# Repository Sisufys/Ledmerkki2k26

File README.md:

The quest for the coolest led overall patch continues....

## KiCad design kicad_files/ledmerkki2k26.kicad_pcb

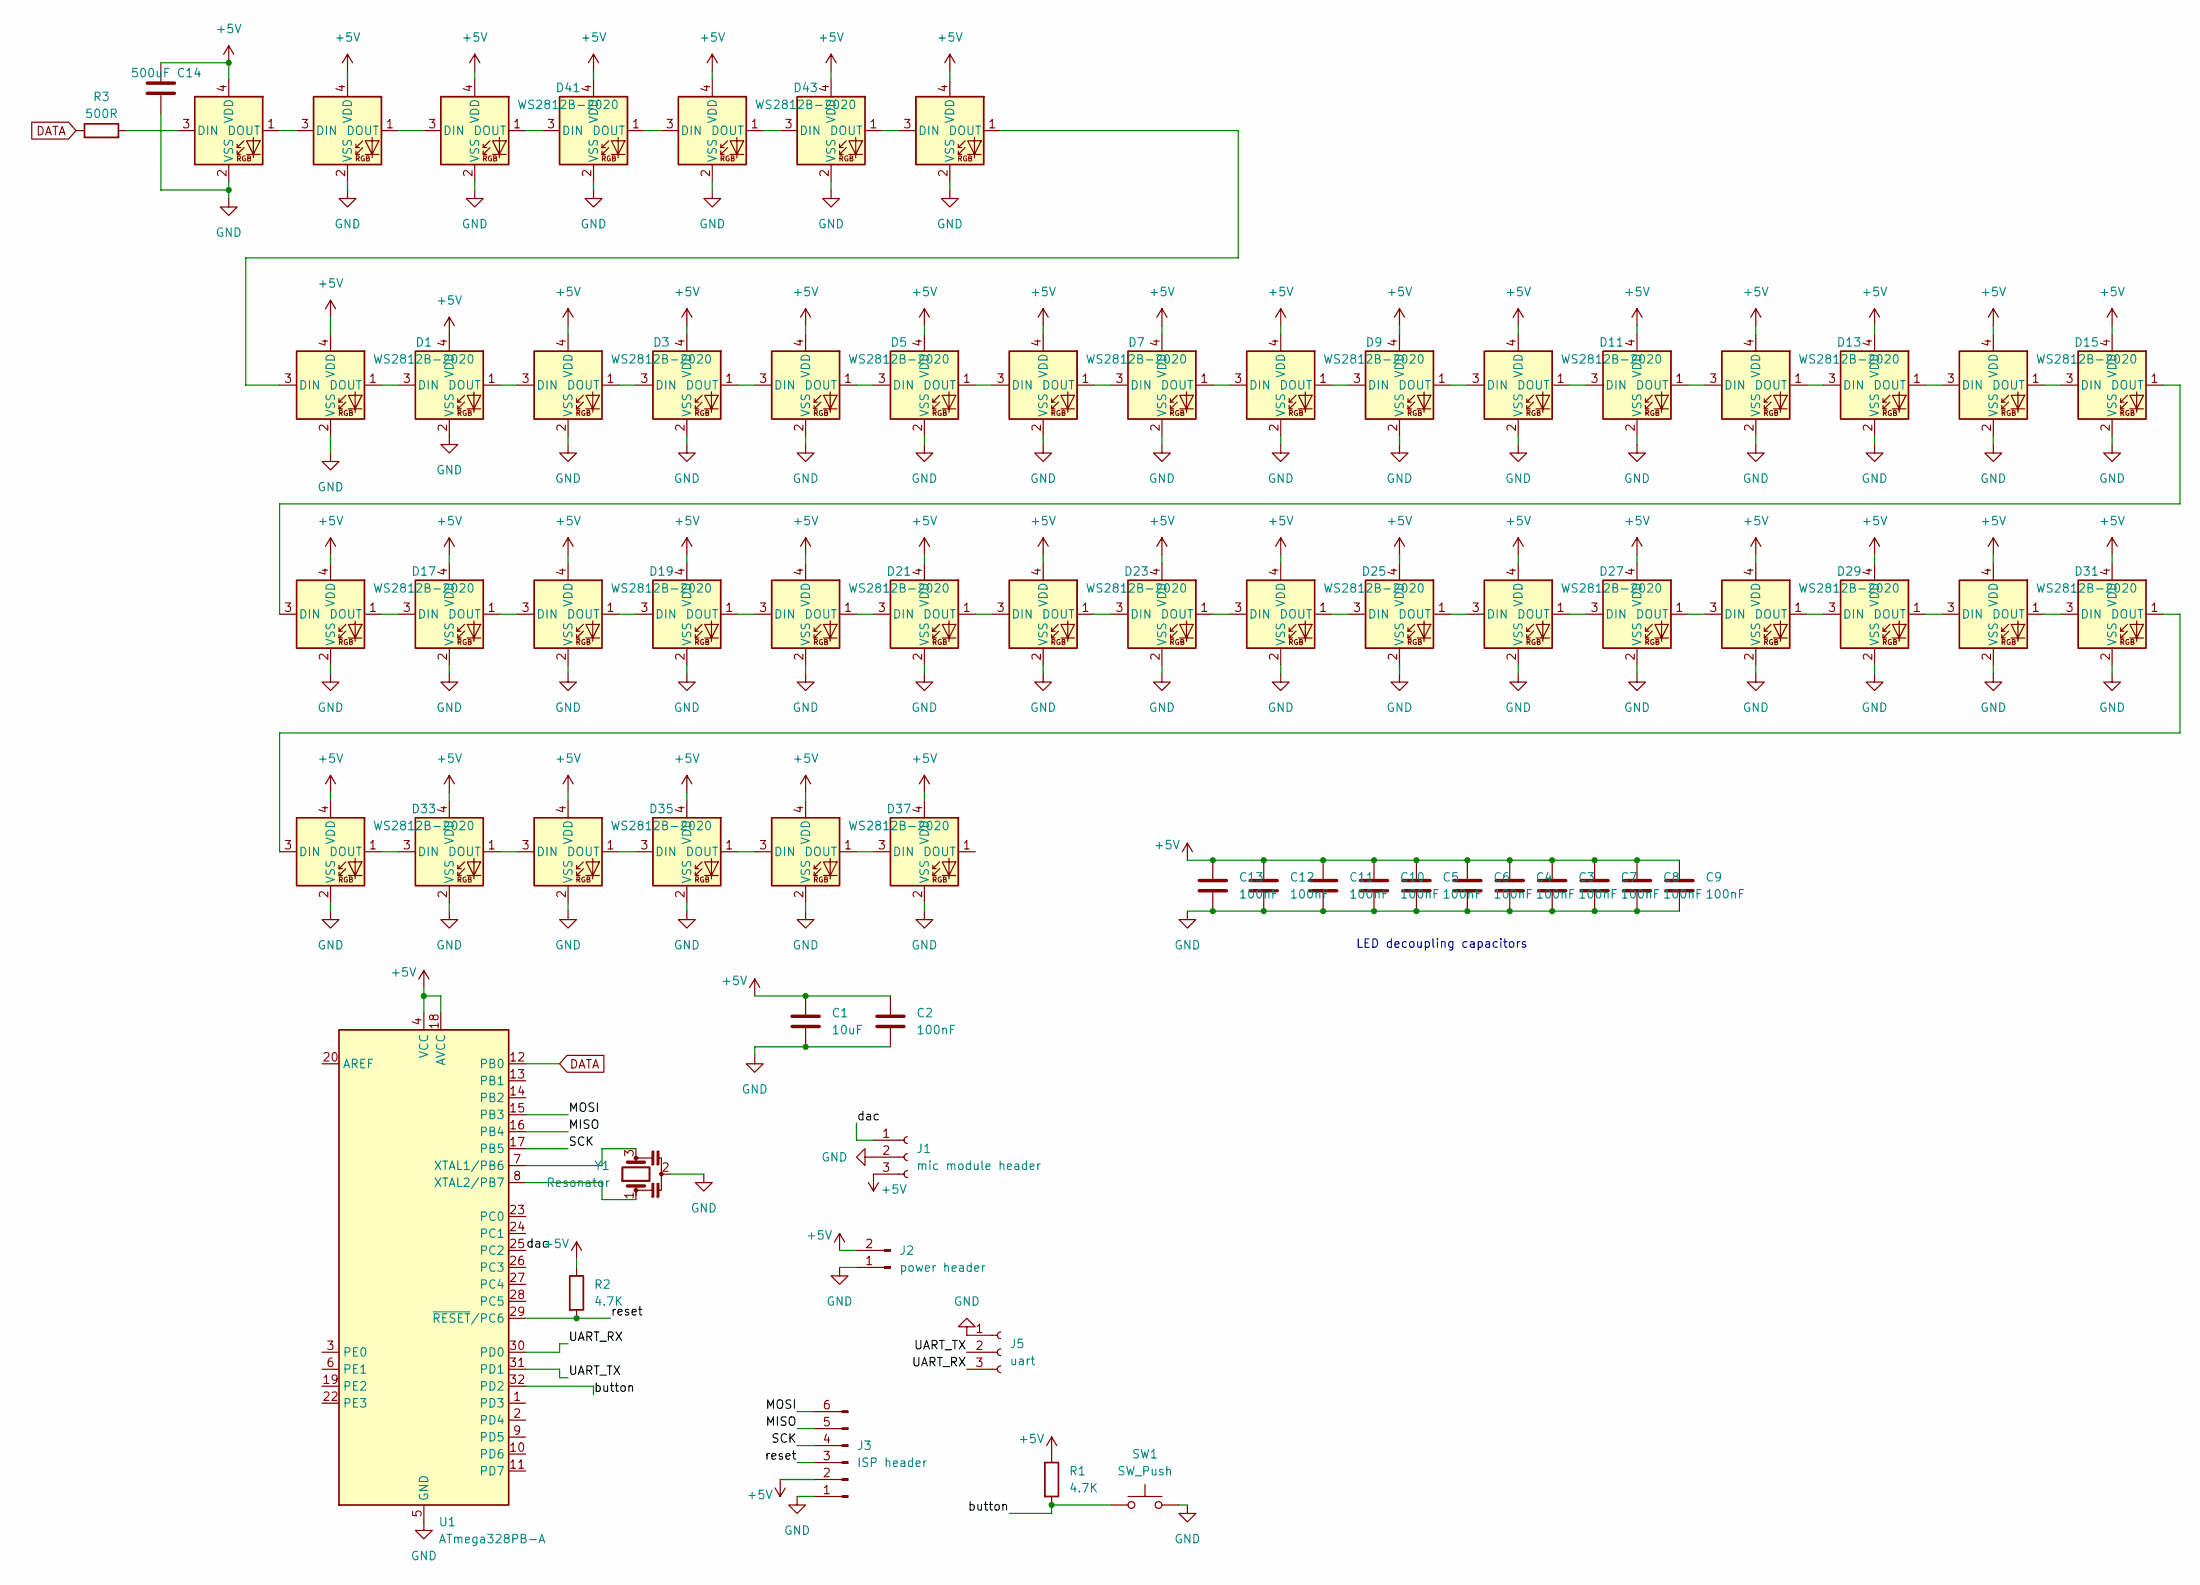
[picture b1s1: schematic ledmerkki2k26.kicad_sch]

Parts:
C1: 10uF; C_1206_3216Metric_Pad1.33x1.80mm_HandSolder
C2, C3, C4, C5, C6, C7, C8, C9, C10, C11, C12, C13: 100nF; C_1206_3216Metric_Pad1.33x1.80mm_HandSolder
C14: 500uF; CP_EIA-7343-15_Kemet-W_HandSolder
D1, D2, D3, D4, D5, D6, D7, D8, D9, D10, D11, D12, D13, D14, D15, D16, D17, D18, D19, D20, D21, D22, D23, D24, D25, D26, D27, D28, D29, D30, D31, D32, D33, D34, D35, D36, D37, D38, D39, D40, D41, D42, D43, D44, D45: WS2812B-2020; LED_WS2812B-2020_PLCC4_2.0x2.0mm
J1: mic module header; PinSocket_1x03_P2.54mm_Vertical
J2: power header; PinHeader_1x02_P2.54mm_Vertical
J3: ISP header; PinHeader_1x06_P2.54mm_Horizontal
J5: uart; PinSocket_1x03_P2.54mm_Vertical
R1, R2: 4.7K; R_0805_2012Metric_Pad1.20x1.40mm_HandSolder
R3: 500R; LED_0805_2012Metric_Pad1.15x1.40mm_HandSolder
SW1: SW_Push; SW_PUSH_6mm
U1: ATmega328PB-A; TQFP-32_7x7mm_P0.8mm
Y1: Resonator; Resonator_SMD_Murata_CSTxExxV-3Pin_3.0x1.1mm_HandSoldering

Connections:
+5V: C1.1, C2.1, C3.1, C4.1, C5.1, C6.1, C7.1, C8.1, C9.1, C10.1, C11.1, C12.1, C13.1, C14.1, D1.4 (VDD), D2.4 (VDD), D3.4 (VDD), D4.4 (VDD), D5.4 (VDD), D6.4 (VDD), D7.4 (VDD), D8.4 (VDD), D9.4 (VDD), D10.4 (VDD), D11.4 (VDD), D12.4 (VDD), D13.4 (VDD), D14.4 (VDD), D15.4 (VDD), D16.4 (VDD), D17.4 (VDD), D18.4 (VDD), D19.4 (VDD), D20.4 (VDD), D21.4 (VDD), D22.4 (VDD), D23.4 (VDD), D24.4 (VDD), D25.4 (VDD), D26.4 (VDD), D27.4 (VDD), D28.4 (VDD), D29.4 (VDD), D30.4 (VDD), D31.4 (VDD), D32.4 (VDD), D33.4 (VDD), D34.4 (VDD), D35.4 (VDD), D36.4 (VDD), D37.4 (VDD), D38.4 (VDD), D39.4 (VDD), D40.4 (VDD), D41.4 (VDD), D42.4 (VDD), D43.4 (VDD), D44.4 (VDD), D45.4 (VDD), J1.3, J2.2, J3.2, R1.1, R2.1, U1.4 (VCC), U1.18 (AVCC); also elsewhere on the board
/MISO: J3.5, U1.16 (PB4)
/MOSI: J3.6, U1.15 (PB3)
/SCK: J3.4, U1.17 (PB5)
/UART_RX: J5.3, U1.30 (PD0)
/UART_TX: J5.2, U1.31 (PD1)
/button: R1.2, SW1.1, U1.32 (PD2)
/dac: J1.1, U1.25 (PC2)
/reset: J3.3, R2.2, U1.29 (~RESET/PC6)
DATA: R3.1, U1.12 (PB0)
GND: C1.2, C2.2, C3.2, C4.2, C5.2, C6.2, C7.2, C8.2, C9.2, C10.2, C11.2, C12.2, C13.2, C14.2, D1.2 (VSS), D2.2 (VSS), D3.2 (VSS), D4.2 (VSS), D5.2 (VSS), D6.2 (VSS), D7.2 (VSS), D8.2 (VSS), D9.2 (VSS), D10.2 (VSS), D11.2 (VSS), D12.2 (VSS), D13.2 (VSS), D14.2 (VSS), D15.2 (VSS), D16.2 (VSS), D17.2 (VSS), D18.2 (VSS), D19.2 (VSS), D20.2 (VSS), D21.2 (VSS), D22.2 (VSS), D23.2 (VSS), D24.2 (VSS), D25.2 (VSS), D26.2 (VSS), D27.2 (VSS), D28.2 (VSS), D29.2 (VSS), D30.2 (VSS), D31.2 (VSS), D32.2 (VSS), D33.2 (VSS), D34.2 (VSS), D35.2 (VSS), D36.2 (VSS), D37.2 (VSS), D38.2 (VSS), D39.2 (VSS), D40.2 (VSS), D41.2 (VSS), D42.2 (VSS), D43.2 (VSS), D44.2 (VSS), D45.2 (VSS), J1.2, J2.1, J3.1, J5.1, SW1.2, U1.5 (GND), U1.21 (GND), Y1.2; also elsewhere on the board
unnamed: D1.3 (DIN), D45.1 (DOUT)
unnamed: D1.1 (DOUT), D2.3 (DIN)
unnamed: D2.1 (DOUT), D3.3 (DIN)
unnamed: D3.1 (DOUT), D4.3 (DIN)
unnamed: D4.1 (DOUT), D5.3 (DIN)
unnamed: D5.1 (DOUT), D6.3 (DIN)
unnamed: D6.1 (DOUT), D7.3 (DIN)
unnamed: D7.1 (DOUT), D8.3 (DIN)
unnamed: D8.1 (DOUT), D9.3 (DIN)
unnamed: D9.1 (DOUT), D10.3 (DIN)
unnamed: D10.1 (DOUT), D11.3 (DIN)
unnamed: D11.1 (DOUT), D12.3 (DIN)
unnamed: D12.1 (DOUT), D13.3 (DIN)
unnamed: D13.1 (DOUT), D14.3 (DIN)
unnamed: D14.1 (DOUT), D15.3 (DIN)
unnamed: D15.1 (DOUT), D16.3 (DIN)
unnamed: D16.1 (DOUT), D17.3 (DIN)
unnamed: D17.1 (DOUT), D18.3 (DIN)
unnamed: D18.1 (DOUT), D19.3 (DIN)
unnamed: D19.1 (DOUT), D20.3 (DIN)
unnamed: D20.1 (DOUT), D21.3 (DIN)
unnamed: D21.1 (DOUT), D22.3 (DIN)
unnamed: D22.1 (DOUT), D23.3 (DIN)
unnamed: D23.1 (DOUT), D24.3 (DIN)
unnamed: D24.1 (DOUT), D25.3 (DIN)
unnamed: D25.1 (DOUT), D26.3 (DIN)
unnamed: D26.1 (DOUT), D27.3 (DIN)
unnamed: D27.1 (DOUT), D28.3 (DIN)
unnamed: D28.1 (DOUT), D29.3 (DIN)
unnamed: D29.1 (DOUT), D30.3 (DIN)
unnamed: D30.1 (DOUT), D31.3 (DIN)
unnamed: D31.1 (DOUT), D32.3 (DIN)
unnamed: D32.1 (DOUT), D33.3 (DIN)
unnamed: D33.1 (DOUT), D34.3 (DIN)
unnamed: D34.1 (DOUT), D35.3 (DIN)
unnamed: D35.1 (DOUT), D36.3 (DIN)
unnamed: D36.1 (DOUT), D37.3 (DIN)
unnamed: D37.1 (DOUT), D38.3 (DIN)
unnamed: D39.3 (DIN), R3.2
unnamed: D39.1 (DOUT), D40.3 (DIN)
unnamed: D40.1 (DOUT), D41.3 (DIN)
unnamed: D41.1 (DOUT), D42.3 (DIN)
unnamed: D42.1 (DOUT), D43.3 (DIN)
unnamed: D43.1 (DOUT), D44.3 (DIN)
unnamed: D44.1 (DOUT), D45.3 (DIN)
unnamed: U1.7 (XTAL1/PB6), Y1.3
unnamed: U1.8 (XTAL2/PB7), Y1.1

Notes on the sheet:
LED decoupling capacitors

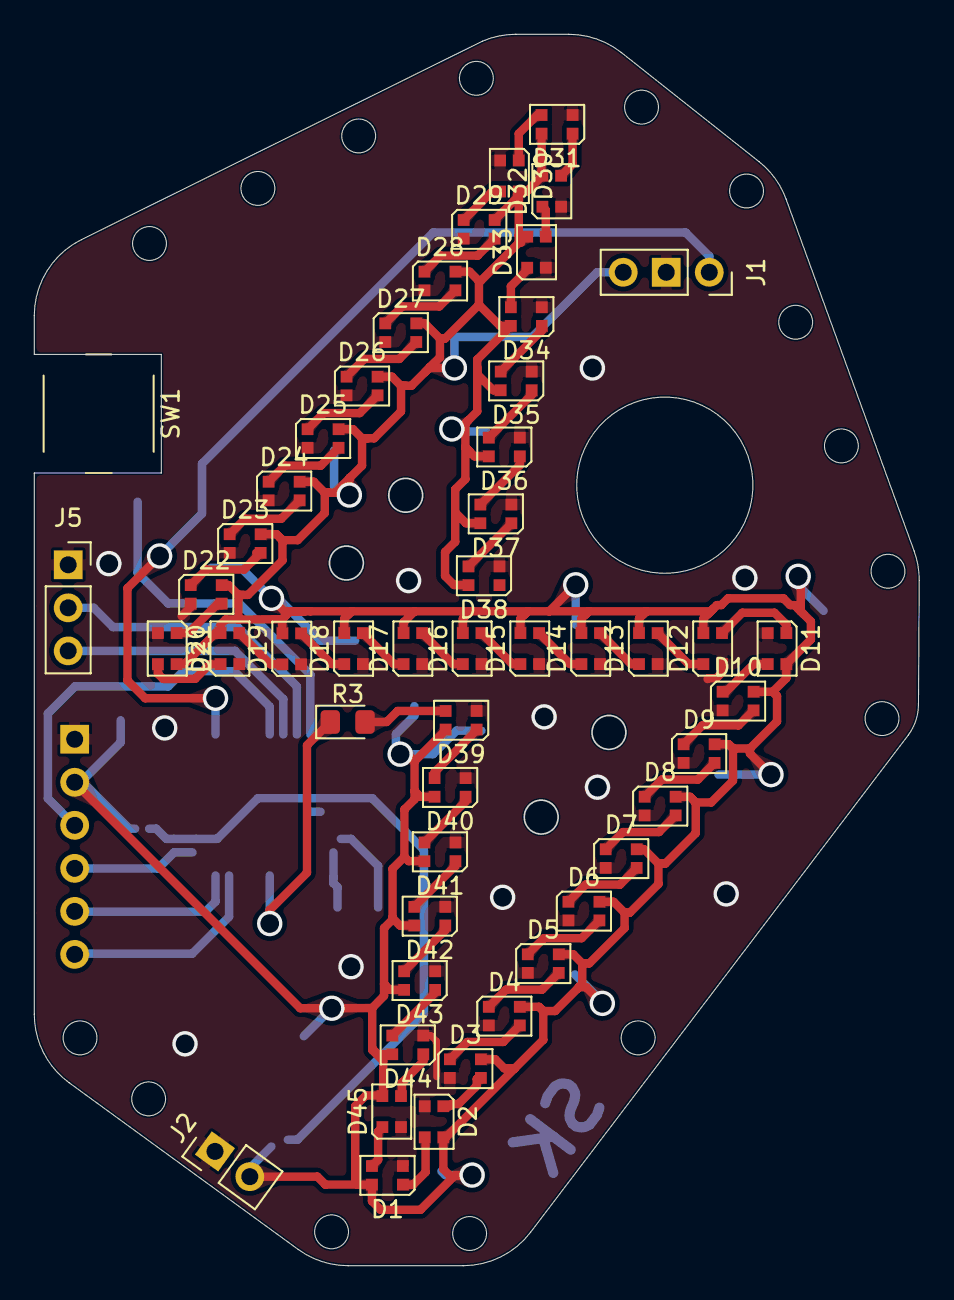
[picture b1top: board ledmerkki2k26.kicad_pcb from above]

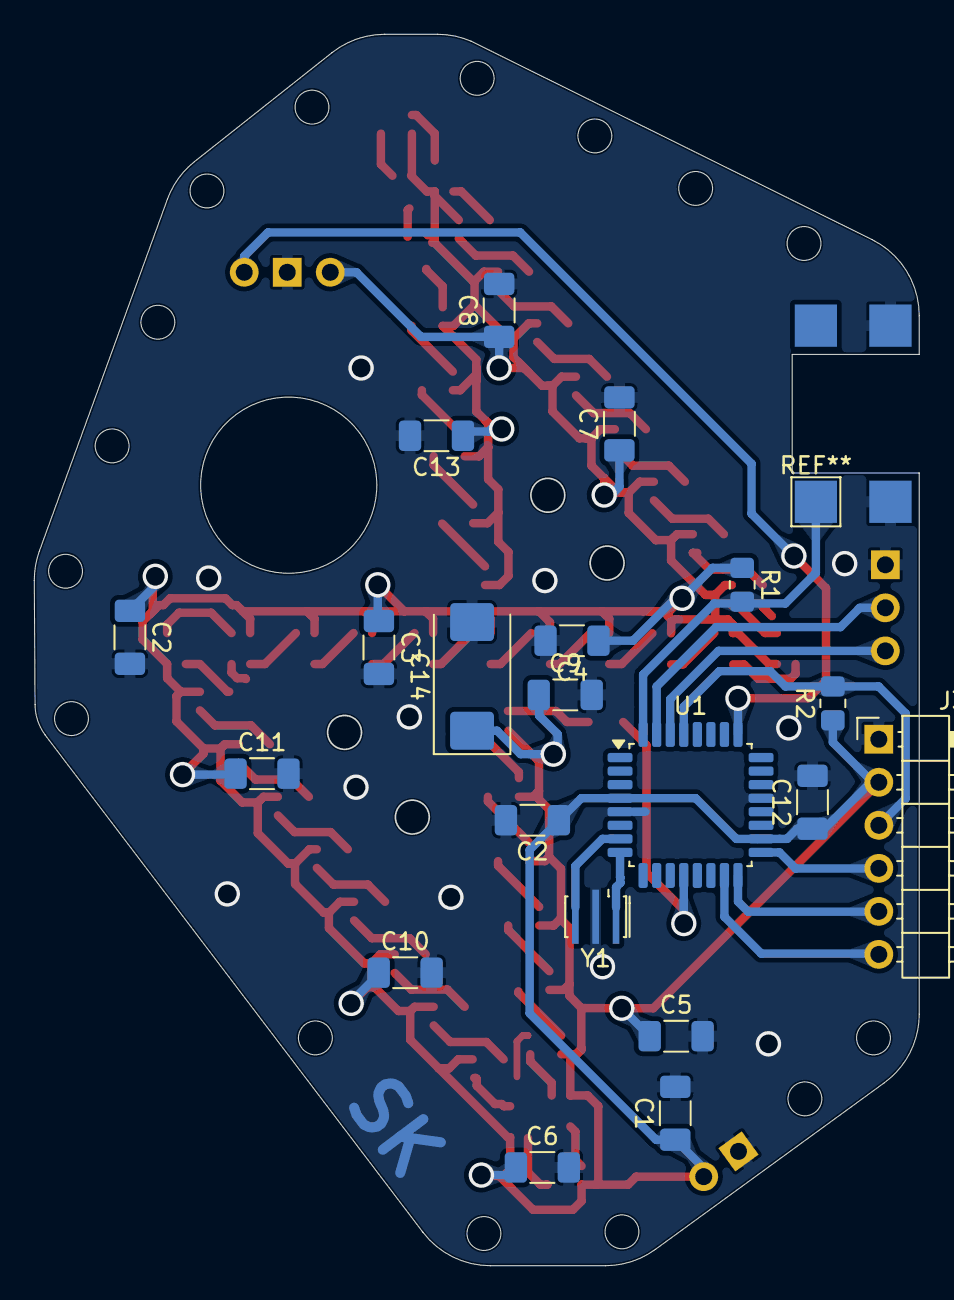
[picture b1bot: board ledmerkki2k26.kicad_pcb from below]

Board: 2 copper layers, 52.2 x 72.7 mm, 70 parts (20 on the bottom side), 58 nets.

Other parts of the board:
C2#2: 100nF; C_1206_3216Metric_Pad1.33x1.80mm_HandSolder

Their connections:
+5V: C2#2.1; also elsewhere on the board
GND: C2#2.2; also elsewhere on the board
